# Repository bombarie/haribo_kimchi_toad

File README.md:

# Jaha Koo - Toad

Code and PCB design for the transmitter and receiver + driver board to control the Toad robot. The wireless control is achieved ising an ExpressLRS wireless link, controlled and read using arduino-compatible microcontrollers. The Toad uses Dynamixel smart servo motors. The host board in the Toad contains a Dynamixel motor driver board, an open-source board designed by [Josue Alejandro Gutierrez](https://github.com/JosueAGtz/dynamixelInterface) and fabbed by me.

Produced for [Campo](https://campo.nu).

## Current files
* Code
  * Toad control from desktop (Chataigne) - [toad_v07_increment_CCs](./chataigne/toad_v07_increment_CCs.noisette)
  * Midi-host transmitter code
    * transmitter #1 (Wemos S2 mini) - [CRServoF_lib_tx_v02_add_midi.cpp](/arduino/platformio/WEMOS_ESP32S2_MIDI_ELRSTX/src/CRServoF_lib_tx_v02_add_midi.cpp)
    * transmitter #2  (Wemos S3 mini) - [CRServoF_lib_tx_v02_add_midi.cpp](./arduino/platformio/wemos_s3_mini/src/CRServoF_lib_tx_v02_add_midi.cpp)
  * Toad receiver code (Xiao esp32-c3): [toad_dynamixel_examples_moveServo_v08_update_to_arduino_core_3.cpp](./arduino/platformio/esp32c3_helloworld/esp32c3_helloworld/src/toad_dynamixel_examples_moveServo_v08_update_to_arduino_core_3.cpp)
* PCB - [toad_mainboard_v03](./kicad/toad%20mainboard%20v01/toad_mainboard_v03/toad_mainboard_v03.kicad_pro)

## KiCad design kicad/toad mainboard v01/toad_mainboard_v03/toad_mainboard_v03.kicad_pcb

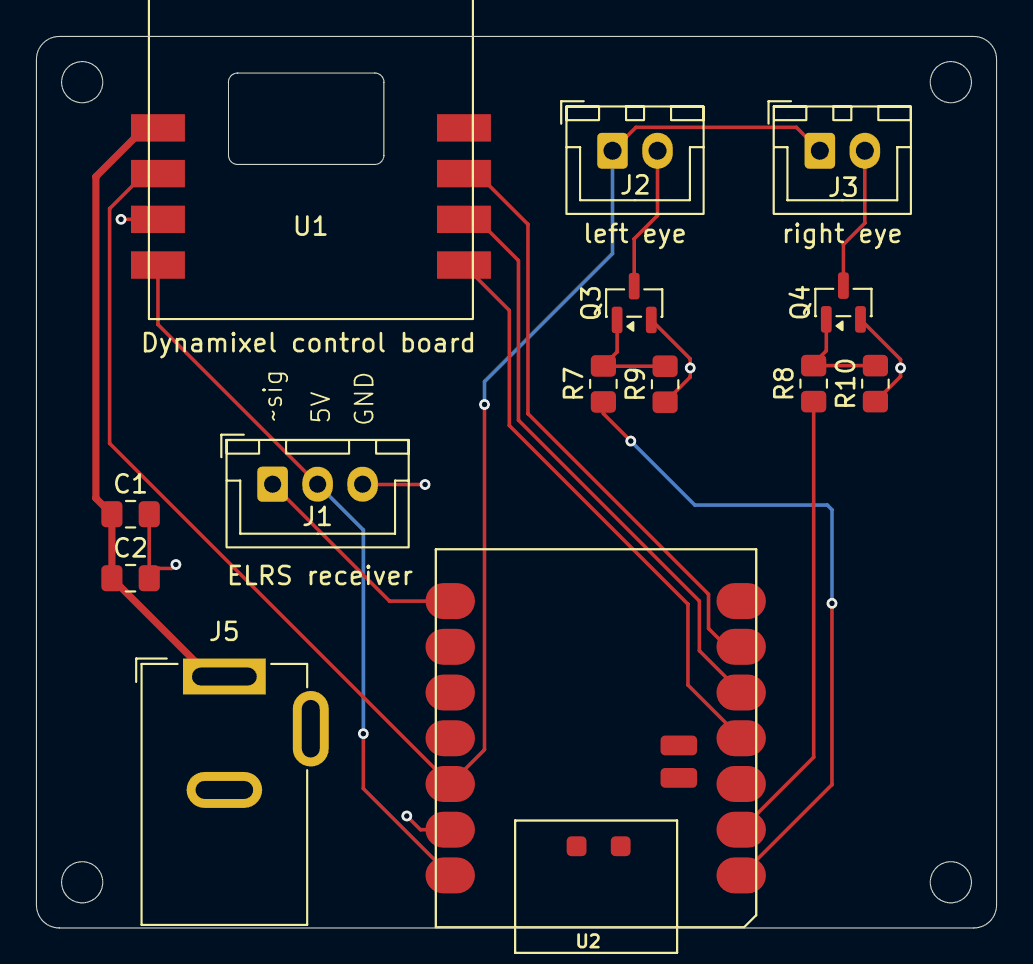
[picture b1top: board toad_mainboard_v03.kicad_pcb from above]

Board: 2 copper layers, 53.3 x 49.5 mm, 14 parts (0 on the bottom side), 14 nets.

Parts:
C1: 1uF; C_0805_2012Metric_Pad1.18x1.45mm_HandSolder
C2: 0.1uF; C_0805_2012Metric_Pad1.18x1.45mm_HandSolder
J1: ELRS receiver; JST_XH_B3B-XH-A_1x03_P2.50mm_Vertical
J2: left eye; JST_XH_B2B-XH-A_1x02_P2.50mm_Vertical
J3: right eye; JST_XH_B2B-XH-A_1x02_P2.50mm_Vertical
J5: Barrel_Jack_Switch; BarrelJack_GCT_DCJ200-10-A_Horizontal
Q3, Q4: BC847; SOT-23
R7, R8: 330; R_0805_2012Metric_Pad1.20x1.40mm_HandSolder
R9, R10: 1k; R_0805_2012Metric_Pad1.20x1.40mm_HandSolder
U1: Dynamixel control board; Dynamixel_driver_board
U2: MOUDLE-SEEEDUINO-XIAO-ESP32C3; MOUDLE14P-SMD-2.54-21X17.8MM

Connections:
3.3V: J2.1, J3.1, U1.6 (VDD), U2.12 (3V3)
5V: J1.2, U1.8 (VCC), U2.14 (5V)
+12V: C1.1, C2.1, J5.1, U1.5 (VMOT)
DMXL_CTRL: U1.3 (CTRL), U2.6 (PA9_A5_D5_SCL)
DMXL_RX: U1.2 (TX), U2.5 (PA8_A4_D4_SDA)
DMXL_TX: U1.1 (RX), U2.4 (PA11_A3_D3)
ELRS_TX: J1.1, U2.8 (PB09_A7_D7_RX)
GND: C1.2, C2.2, J1.3, J5.2, Q3.2 (E), Q4.2 (E), R9.1, R10.1, U1.7 (GND), U2.13 (GND)
LEFT_EYE: R7.1, U2.1 (PA02_A0_D0)
unnamed: J2.2, Q3.3 (C)
unnamed: J3.2, Q4.3 (C)
unnamed: Q3.1 (B), R7.2, R9.2
unnamed: Q4.1 (B), R8.2, R10.2
RIGHT_EYE: R8.1, U2.2 (PA4_A1_D1)

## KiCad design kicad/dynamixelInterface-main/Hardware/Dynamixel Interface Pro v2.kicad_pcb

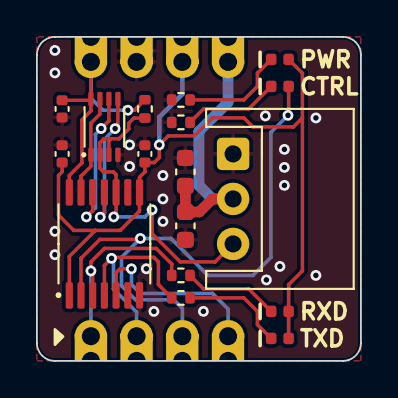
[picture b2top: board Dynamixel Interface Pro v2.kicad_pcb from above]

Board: 2 copper layers, 18.0 x 18.0 mm, 19 parts (1 on the bottom side), 16 nets.

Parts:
C1: 1uF; C_0402_1005Metric
C2, C5: 0.1uF; C_0402_1005Metric
C3: 10uF; C_0603_1608Metric
C4: 1uF; C_0603_1608Metric
D1, D2: Orange; 0402LED
D3: Blue; 0402LED
D4: Green; 0402LED
FP0: Dynamixel PRO; Dynamixel_Driver
G_logoSmall: LOGO; G_SELOGO_SMALL
J1: Conn_01x03_Socket; JST_EH_S3B-EH_1x03_P2.50mm_Horizontal
R1, R2, R3, R4: 1K; R_0402_1005Metric
R5: 10K; R_0402_1005Metric
U1: TXB0104PWR; TSSOP14_5x4.4_0.65
U2: SN74LVC2G241DCTR; VSSOP-8_2.3x2mm_P0.5mm

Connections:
CTRL: U1.13 (B1), U2.1 (1OE), U2.7 (2OE)
CTRLL: D3.2 (A), FP0.3 (CTRL), U1.2 (A1)
DATA: J1.3, R5.2, U1.10 (B4), U2.2 (1A), U2.3 (2Y)
DATAL: FP0.4 (DATAL), U1.5 (A4)
GND: C1.2, C2.2, C3.2, C4.2, C5.2, FP0.7 (GND), J1.1, R3.2, R4.2, U1.7 (GND), U2.4 (GND)
unnamed: D1.1 (K), R1.1
unnamed: D2.1 (K), R2.1
unnamed: D3.1 (K), R3.1
unnamed: D4.1 (K), R4.1
RXD: U1.12 (B2), U2.6 (1Y)
RXDL: FP0.1 (RXD), R1.2, U1.3 (A2)
TXD: U1.11 (B3), U2.5 (2A)
TXDL: FP0.2 (TXD), R2.2, U1.4 (A3)
VCC: C2.1, FP0.8 (VDD), R5.1, U1.14 (VCCB), U2.8 (VCC)
VDC: C3.1, C4.1, FP0.5 (DATA), J1.2
VDD: C1.1, C5.1, D1.2 (A), D2.2 (A), D4.2 (A), FP0.6 (VMOT), U1.1 (VCCA), U1.8 (OE)

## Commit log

2026-04-02 add gitignores
2026-04-02 add xiao esp32c3 code
2026-04-02 add xiao esp32s3 code
2026-04-02 add wemos esp32s2 code
2026-04-02 Create haribo_kimchi_toad.code-workspace
2026-04-23 add CRSF lib to esp32c3 project
2026-04-23 add CRSF lib to esp32s2 project
2026-04-23 add CRSF lib to esp32s3 project
2026-04-23 create esp32s3 project (copy from esp32s2 project)
2026-04-23 set esp32s3 project config
2026-04-23 update xiao_esp32s3 project config
2026-04-23 add CRSF lib to xiao_esp32s3 project
2026-04-23 esp32c3 - add scripts and update project config
2026-04-23 xiao_esp32s3 - add/update scripts
2026-04-23 wemos_esp32s2 - add scripts and update project config
2026-04-23 wemos_esp32s3 - add/update scripts
2026-04-23 Update haribo_kimchi_toad.code-workspace
2026-04-23 add cad files
2026-04-23 add Dynamixel driver board project
2026-04-23 add interactive bom
2026-04-23 add toad host pcb project
2026-04-23 add custom Kicad footprints and symbols
2026-04-23 add manuals
